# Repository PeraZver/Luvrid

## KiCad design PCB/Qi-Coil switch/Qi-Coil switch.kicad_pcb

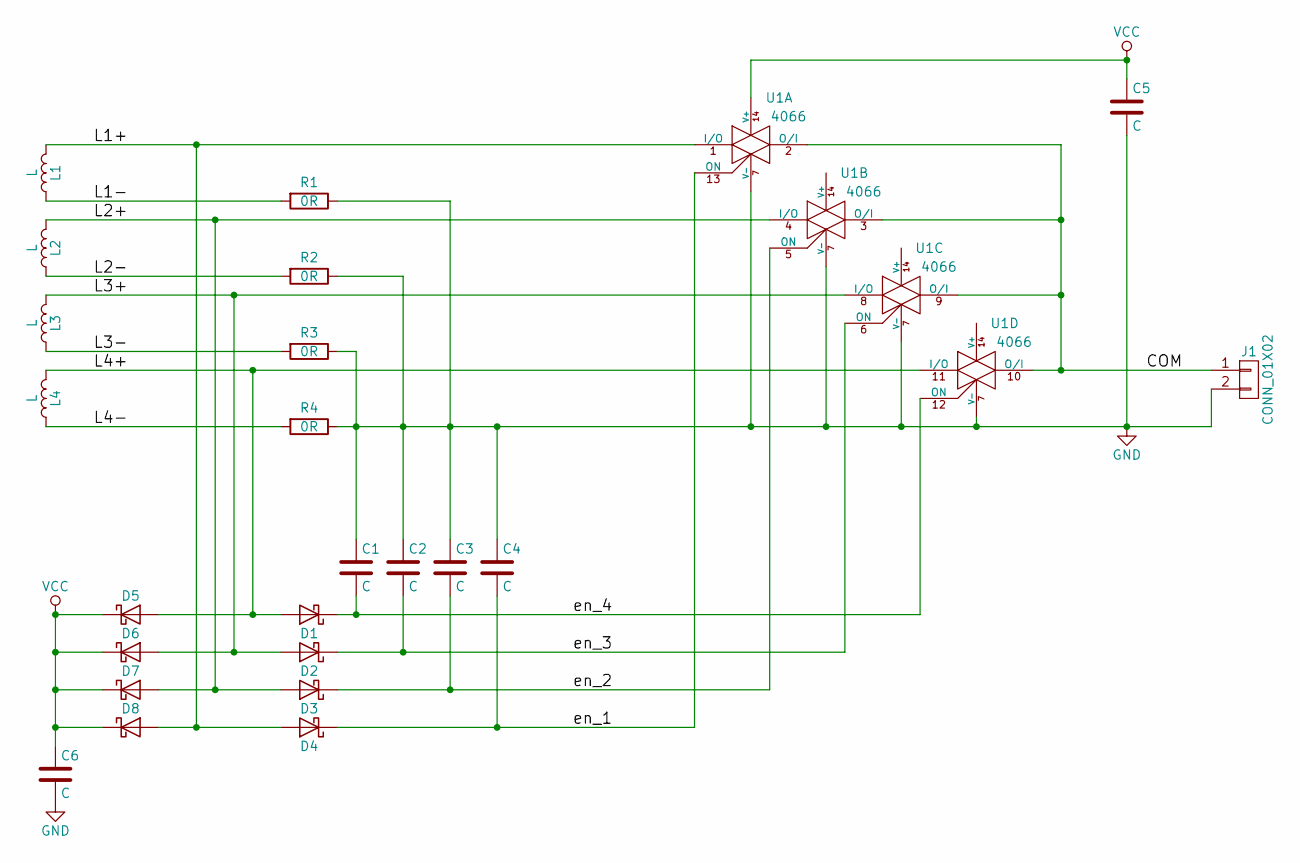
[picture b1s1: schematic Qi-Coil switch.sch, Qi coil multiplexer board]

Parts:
C1, C2, C3, C4, C6: C; C_0603_HandSoldering
C5: C; C_0805_HandSoldering
D1, D2, D3, D4, D5, D6, D7, D8: D_Schottky; D_SMB_Handsoldering
J1: CONN_01X02; Pin_Header_Straight_1x02_Pitch2.54mm
L1, L2, L3, L4: L; Pin_Header_Straight_1x02_Pitch2.54mm
R1, R2, R3, R4: 0R; R_0603_HandSoldering
U1: 4066; SSOP-14

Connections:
/COM: J1.1, U1.2 (O/I), U1.3 (O/I), U1.9 (O/I), U1.10 (O/I)
/L1+: D4.2 (A), D8.2 (A), L1.2, U1.1 (I/O)
/L1-: L1.1, R1.2
/L2+: D3.2 (A), D7.2 (A), L2.2, U1.4 (I/O)
/L2-: L2.1, R2.2
/L3+: D2.2 (A), D6.2 (A), L3.2, U1.8 (I/O)
/L3-: L3.1, R3.2
/L4+: D1.2 (A), D5.2 (A), L4.2, U1.11 (I/O)
/L4-: L4.1, R4.2
/en_1: C4.2, D4.1 (K), U1.13 (ON)
/en_2: C3.2, D3.1 (K), U1.5 (ON)
/en_3: C2.2, D2.1 (K), U1.6 (ON)
/en_4: C1.2, D1.1 (K), U1.12 (ON)
GND: C1.1, C2.1, C3.1, C4.1, C5.2, C6.2, J1.2, R1.1, R2.1, R3.1, R4.1, U1.7 (V-)
VCC: C5.1, C6.1, D5.1 (K), D6.1 (K), D7.1 (K), D8.1 (K), U1.14 (V+)

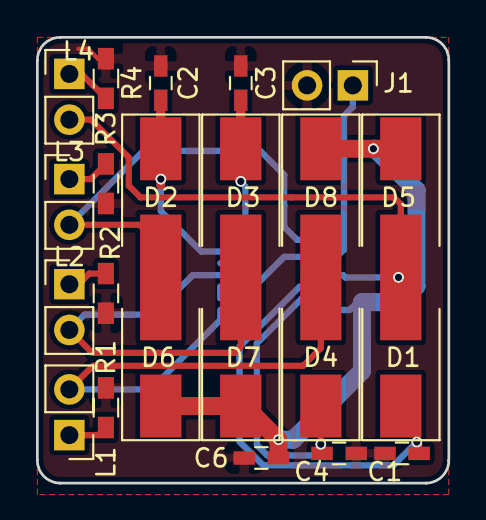
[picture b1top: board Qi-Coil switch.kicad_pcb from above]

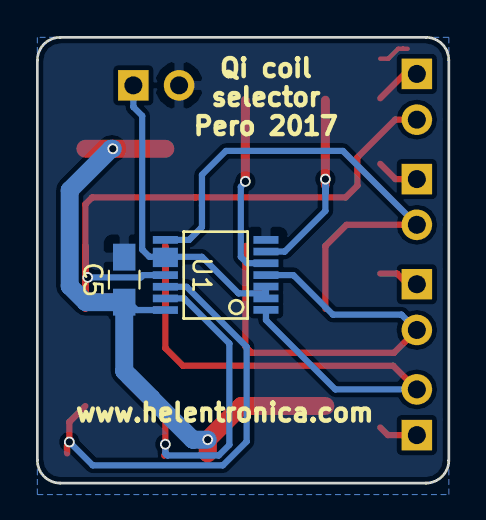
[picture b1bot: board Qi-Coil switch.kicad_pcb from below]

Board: 2 copper layers, 22.9 x 24.8 mm, 24 parts (2 on the bottom side), 15 nets.

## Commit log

2016-03-09 First commit of the Loveread Lamp Project.
2016-03-09 Just testing the commits with some stupit comment change
2016-03-09 Still playing with GIT - this time I wanted to see how does it recognize the changes in Eagle files.
2016-03-12 Limit rotation within the range of palm turn.
    Light intensity goes from 20 to 255 as much as you can turn your hand
    simply.
2016-07-17 added gitignore file
2016-07-17 Symmetrical Intensity calculation for both lamps
2016-07-26 added 3D models
2016-07-26 Add 3D model
2016-07-26 remove datasheets
2016-07-31 Adding Qi receiver modules
2016-07-31 Adding Tiny163 4 instead of mega32u4
2016-08-02 Two-sheet schematics, and routing Qi chargers
2016-08-23 Qi chargers routed
2016-08-25 LED driver changed
2016-08-25 Adds buck converter
2016-08-26 rerouted Qi chargers and finished arrangements
2016-08-26 Component placement
2016-08-27 routing finished
2016-08-27 DRC done
2016-08-28 gerber generated
2016-08-28 remove pdf files
2016-08-29 improved spacing, added silkscreen
2016-08-29 fix untracked files
2016-08-30 fabrication output generated
2016-09-01 finished 3D model
2016-11-13 going back to 32u4
2016-11-13 started routing with 32u4
2016-11-15 order complete
2017-02-26 version 3.0 complete release
2017-03-05 modified code to run on 8MHz atmega 32u4
2017-04-19 set system clock to 8 MHz
2017-05-08 no xtal and no transistor LED drivers
2017-09-24 qi coil switch prototype
2017-09-24 rm unnecessary code examples
